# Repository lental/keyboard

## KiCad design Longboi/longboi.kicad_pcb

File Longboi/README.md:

http://www.keyboard-layout-editor.com/#/gists/9dde3a739abcb1b83a87db58105d393a

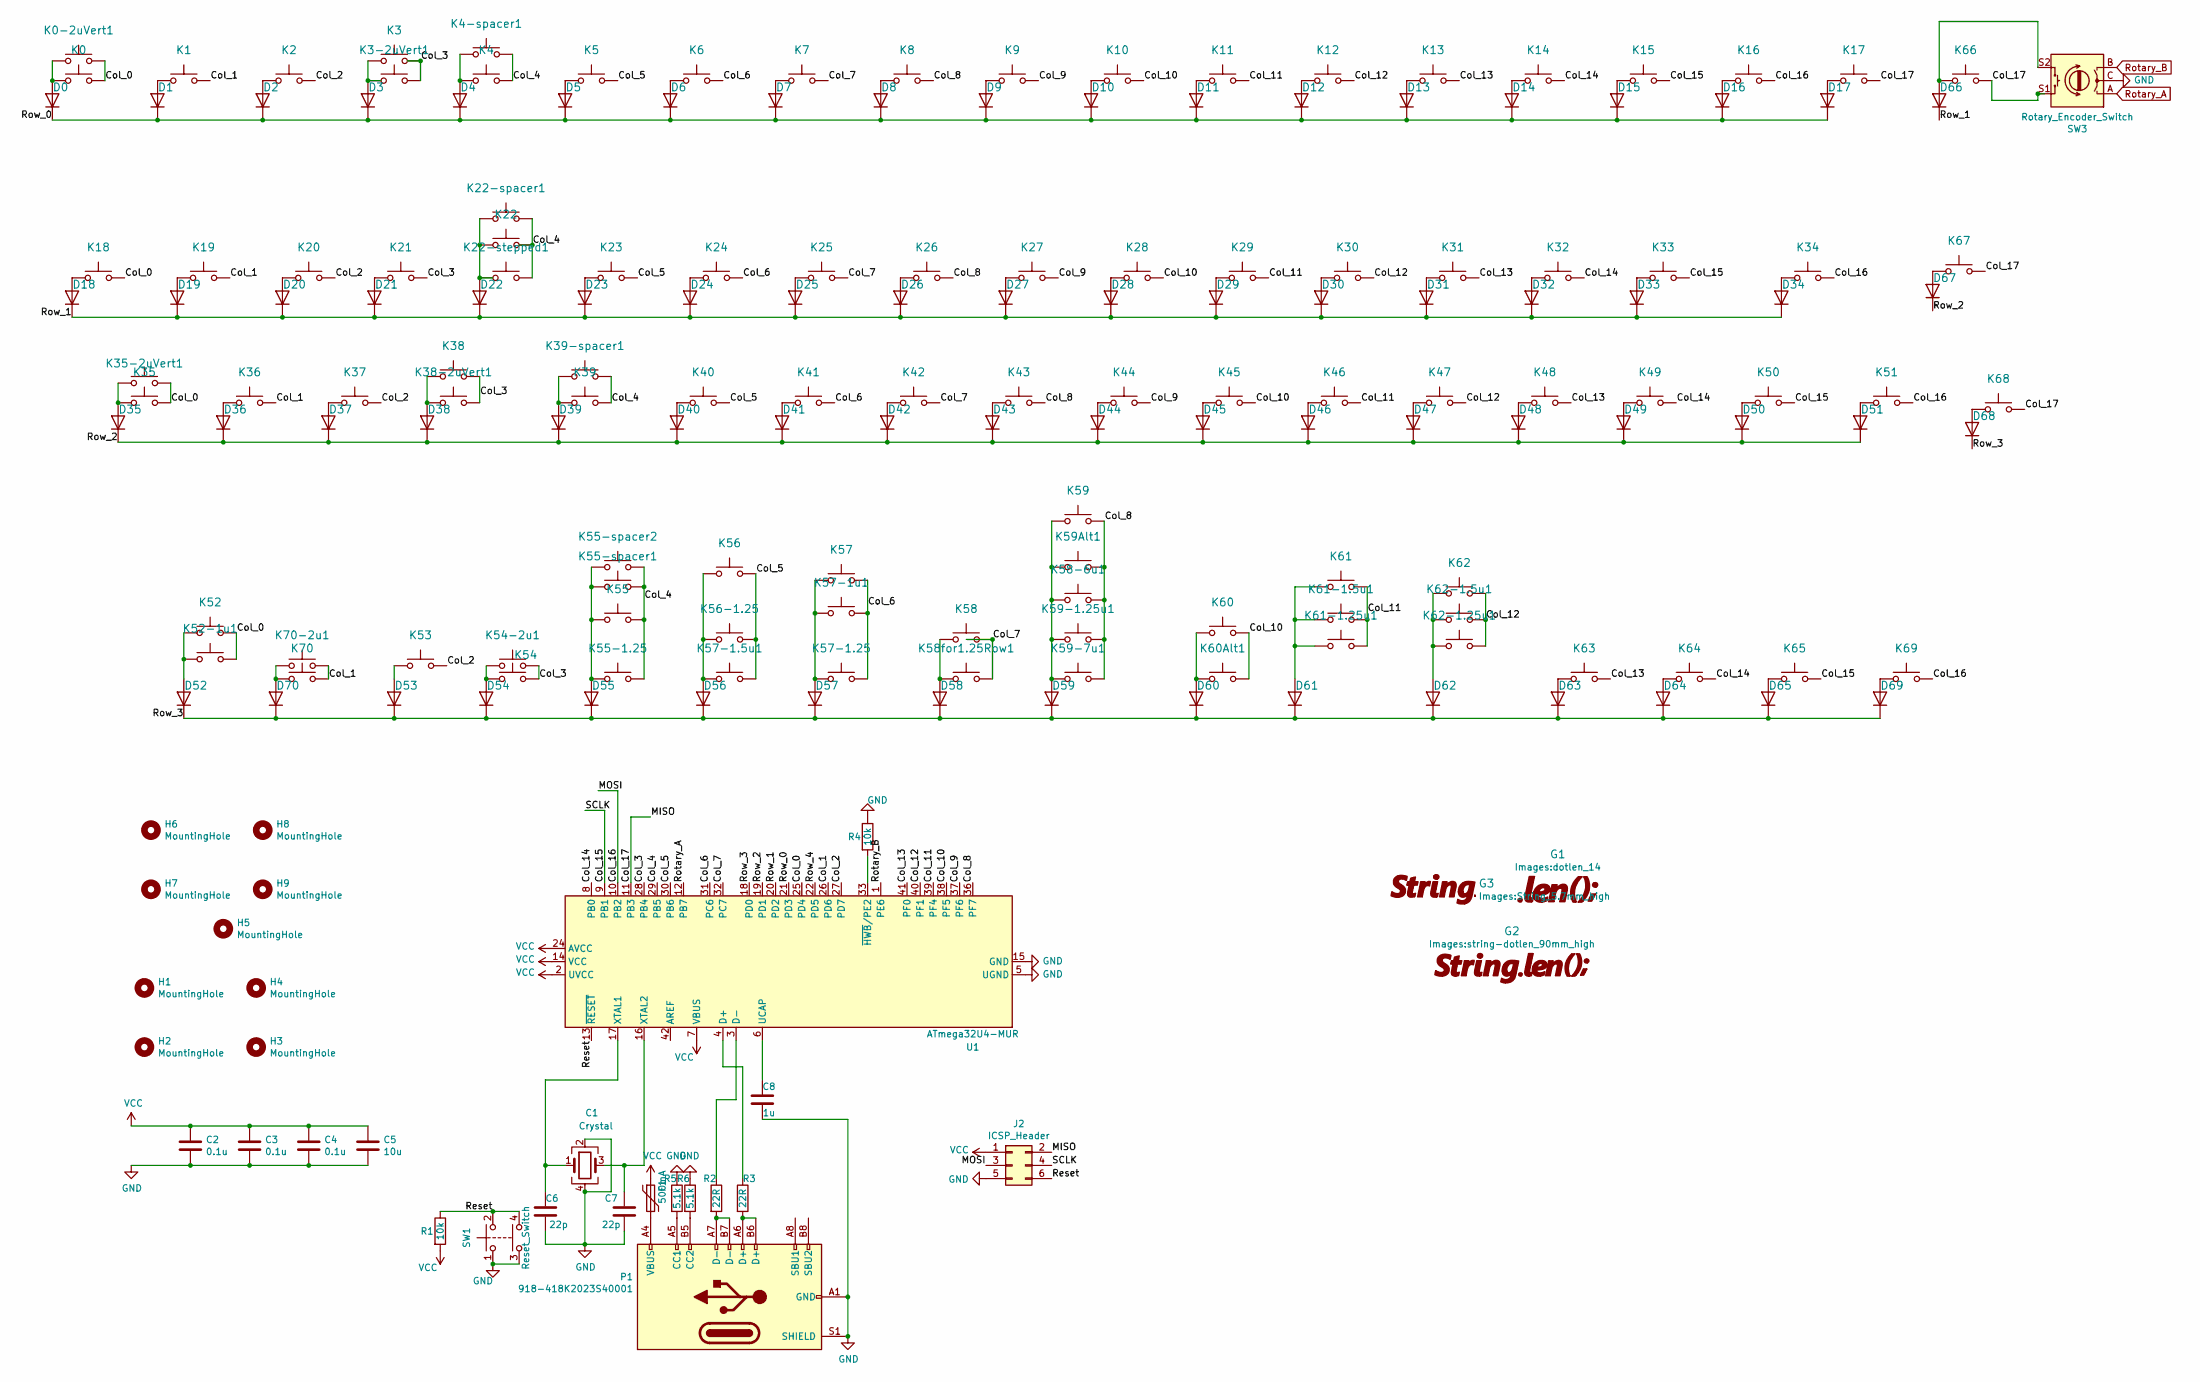
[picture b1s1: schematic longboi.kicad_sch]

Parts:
C1: Crystal; Crystal_SMD_3225-4Pin_3.2x2.5mm
C2, C3, C4: 0.1u; C_0805_2012Metric_Pad1.15x1.40mm_HandSolder
C5: 10u; C_0805_2012Metric_Pad1.15x1.40mm_HandSolder
C6, C7: 22p; C_0805_2012Metric_Pad1.15x1.40mm_HandSolder
C8: 1u; C_0805_2012Metric_Pad1.15x1.40mm_HandSolder
D0, D1, D2, D3, D4, D5, D6, D7, D8, D9, D10, D11, D12, D13, D14, D15, D16, D17, D18, D19, D20, D21, D22, D23, D24, D25, D26, D27, D28, D29, D30, D31, D32, D33, D34, D35, D36, D37, D38, D39, D40, D41, D42, D43, D44, D45, D46, D47, D48, D49, D50, D51, D52, D53, D54, D55, D56, D57, D58, D59, D60, D61, D62, D63, D64, D65, D66, D67, D68, D69, D70: SOD-323F; D_SOD-323F
F1: 500mA; Fuse_1206_3216Metric
G1: dotlen; dotlen_14
G2: string_dotlen; string-dotlen_90mm_high
G3: string; String_5.7mm_high
H1, H2, H3, H4, H5, H6, H7, H8, H9: MountingHole; M2 Mounting Hole
J2: ICSP_Header; PinHeader_2x03_P2.54mm_Vertical
K0, K1, K2, K3, K4-spacer1, K5, K6, K7, K8, K9, K10, K11, K12, K13, K14, K15, K16, K18, K19, K20, K21, K23, K24, K25, K26, K27, K28, K29, K30, K31, K32, K33, K35, K36, K37, K38, K40, K41, K42, K43, K44, K45, K46, K47, K48, K49, K51, K52-1u1, K53, K54, K55-spacer2, K57-1u1, K59, K60Alt1, K61, K62, K63, K64, K65, K66, K67, K68, K69, K70: KEYSW; MXOnly-1U-NoLED
K0-2uVert1, K35-2uVert1, K52, K54-2u1, K70-2u1: KEYSW; MXOnly-2U-ReversedStabilizers-NoLED
K3-2uVert1, K38-2uVert1: KEYSW; MXOnly-2U-NoLED
K4, K17, K55, K57-1.5u1, K61-1.5u1, K62-1.5u1: KEYSW; MXOnly-1.5U-NoLED
K22, K39-spacer1, K50: KEYSW; MXOnly-1.75U-NoLED
K22-spacer1, K22-stepped1, K55-1.25, K55-spacer1, K56, K56-1.25, K57, K57-1.25, K59-1.25u1, K61-1.25u1, K62-1.25u1: KEYSW; MXOnly-1.25U-NoLED
K34, K39, K58, K58for1.25Row1: KEYSW; MXOnly-2.25U-ReversedStabilizers-NoLED
K58-6u1: KEYSW; MXOnly-6.25U-ReversedStabilizers-NoLED
K59-7u1: KEYSW; MXOnly-7U-ReversedStabilizers-NoLED
K59Alt1, K60: KEYSW; MXOnly-2.75U-ReversedStabilizers-NoLED
P1: 918-418K2023S40001
R1, R4: 10k; R_0805_2012Metric_Pad1.15x1.40mm_HandSolder
R2, R3: 22R; R_0805_2012Metric_Pad1.15x1.40mm_HandSolder
R5, R6: 5.1k; R_0805_2012Metric_Pad1.15x1.40mm_HandSolder
SW1: Reset_Switch; SKQG-1155865
SW3: Rotary_Encoder_Switch; RotaryEncoder_Alps_EC11E-Switch_Vertical_H20mm_MX-1U
U1: ATmega32U4-MUR; QFN-44-1EP_7x7mm_P0.5mm_EP5.2x5.2mm

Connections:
/Col_0: K0.2, K0-2uVert1.2, K18.2, K35.2, K35-2uVert1.2, K52.2, K52-1u1.2, U1.25 (PD4)
/Col_1: K1.2, K19.2, K36.2, K70.2, K70-2u1.2, U1.26 (PD6)
/Col_2: K2.2, K20.2, K37.2, K53.2, U1.27 (PD7)
/Col_3: K3.2, K3-2uVert1.2, K21.2, K38.2, K38-2uVert1.2, K54.2, K54-2u1.2, U1.28 (PB4)
/Col_4: K4.2, K4-spacer1.2, K22.2, K22-spacer1.2, K22-stepped1.2, K39.2, K39-spacer1.2, K55.2, K55-1.25.2, K55-spacer1.2, K55-spacer2.2, U1.29 (PB5)
/Col_5: K5.2, K23.2, K40.2, K56.2, K56-1.25.2, K57-1.5u1.2, U1.30 (PB6)
/Col_6: K6.2, K24.2, K41.2, K57.2, K57-1.25.2, K57-1u1.2, U1.31 (PC6)
/Col_7: K7.2, K25.2, K42.2, K58.2, K58for1.25Row1.2, U1.32 (PC7)
/Col_8: K8.2, K26.2, K43.2, K58-6u1.2, K59.2, K59-1.25u1.2, K59-7u1.2, K59Alt1.2, U1.36 (PF7)
/Col_9: K9.2, K27.2, K44.2, U1.37 (PF6)
/Col_10: K10.2, K28.2, K45.2, K60.2, K60Alt1.2, U1.38 (PF5)
/Col_11: K11.2, K29.2, K46.2, K61.2, K61-1.5u1.2, K61-1.25u1.2, U1.39 (PF4)
/Col_12: K12.2, K30.2, K47.2, K62.2, K62-1.5u1.2, K62-1.25u1.2, U1.40 (PF1)
/Col_13: K13.2, K31.2, K48.2, K63.2, U1.41 (PF0)
/Col_14: K14.2, K32.2, K49.2, K64.2, U1.8 (PB0)
/Col_15: J2.4, K15.2, K33.2, K50.2, K65.2, U1.9 (PB1)
/Col_16: J2.3, K16.2, K34.2, K51.2, K69.2, U1.10 (PB2)
/Col_17: J2.2, K17.2, K66.2, K67.2, K68.2, SW3.S1, U1.11 (PB3)
/Reset: J2.6, R1.1, SW1.2, SW1.4, U1.13 (~RESET)
/Row_0: D0.1 (K), D1.1 (K), D2.1 (K), D3.1 (K), D4.1 (K), D5.1 (K), D6.1 (K), D7.1 (K), D8.1 (K), D9.1 (K), D10.1 (K), D11.1 (K), D12.1 (K), D13.1 (K), D14.1 (K), D15.1 (K), D16.1 (K), D17.1 (K), U1.21 (PD3)
/Row_1: D18.1 (K), D19.1 (K), D20.1 (K), D21.1 (K), D22.1 (K), D23.1 (K), D24.1 (K), D25.1 (K), D26.1 (K), D27.1 (K), D28.1 (K), D29.1 (K), D30.1 (K), D31.1 (K), D32.1 (K), D33.1 (K), D34.1 (K), D66.1 (K), U1.20 (PD2)
/Row_2: D35.1 (K), D36.1 (K), D37.1 (K), D38.1 (K), D39.1 (K), D40.1 (K), D41.1 (K), D42.1 (K), D43.1 (K), D44.1 (K), D45.1 (K), D46.1 (K), D47.1 (K), D48.1 (K), D49.1 (K), D50.1 (K), D51.1 (K), D67.1 (K), U1.19 (PD1)
/Row_3: D52.1 (K), D53.1 (K), D54.1 (K), D55.1 (K), D56.1 (K), D57.1 (K), D58.1 (K), D59.1 (K), D60.1 (K), D61.1 (K), D62.1 (K), D63.1 (K), D64.1 (K), D65.1 (K), D68.1 (K), D69.1 (K), D70.1 (K), U1.18 (PD0)
/Row_4: U1.22 (PD5)
GND: C1.2, C1.4, C2.2, C3.2, C4.2, C5.2, C6.2, C7.2, C8.2, J2.5, P1.A1 (GND), P1.A12 (GND), P1.B1 (GND), P1.B12 (GND), P1.S1 (SHIELD), R4.1, R5.1, R6.1, SW1.1, SW1.3, SW3.C, U1.5 (UGND), U1.15 (GND), U1.23 (GND), U1.35 (GND), U1.43 (GND), U1.45 (GND)
unnamed: C1.1, C6.1, U1.17 (XTAL1)
unnamed: C1.3, C7.1, U1.16 (XTAL2)
unnamed: C8.1, U1.6 (UCAP)
unnamed: D0.2 (A), K0.1, K0-2uVert1.1
unnamed: D1.2 (A), K1.1
unnamed: D2.2 (A), K2.1
unnamed: D3.2 (A), K3.1, K3-2uVert1.1
unnamed: D4.2 (A), K4.1, K4-spacer1.1
unnamed: D5.2 (A), K5.1
unnamed: D6.2 (A), K6.1
unnamed: D7.2 (A), K7.1
unnamed: D8.2 (A), K8.1
unnamed: D9.2 (A), K9.1
unnamed: D10.2 (A), K10.1
unnamed: D11.2 (A), K11.1
unnamed: D12.2 (A), K12.1
unnamed: D13.2 (A), K13.1
unnamed: D14.2 (A), K14.1
unnamed: D15.2 (A), K15.1
unnamed: D16.2 (A), K16.1
unnamed: D17.2 (A), K17.1
unnamed: D18.2 (A), K18.1
unnamed: D19.2 (A), K19.1
unnamed: D20.2 (A), K20.1
unnamed: D21.2 (A), K21.1
unnamed: D22.2 (A), K22.1, K22-spacer1.1, K22-stepped1.1
unnamed: D23.2 (A), K23.1
unnamed: D24.2 (A), K24.1
unnamed: D25.2 (A), K25.1
unnamed: D26.2 (A), K26.1
unnamed: D27.2 (A), K27.1
unnamed: D28.2 (A), K28.1
unnamed: D29.2 (A), K29.1
unnamed: D30.2 (A), K30.1
unnamed: D31.2 (A), K31.1
unnamed: D32.2 (A), K32.1
unnamed: D33.2 (A), K33.1
unnamed: D34.2 (A), K34.1
unnamed: D35.2 (A), K35.1, K35-2uVert1.1
unnamed: D36.2 (A), K36.1
unnamed: D37.2 (A), K37.1
unnamed: D38.2 (A), K38.1, K38-2uVert1.1
unnamed: D39.2 (A), K39.1, K39-spacer1.1
unnamed: D40.2 (A), K40.1
unnamed: D41.2 (A), K41.1
unnamed: D42.2 (A), K42.1
unnamed: D43.2 (A), K43.1
unnamed: D44.2 (A), K44.1
unnamed: D45.2 (A), K45.1
unnamed: D46.2 (A), K46.1
unnamed: D47.2 (A), K47.1
unnamed: D48.2 (A), K48.1
unnamed: D49.2 (A), K49.1
unnamed: D50.2 (A), K50.1
unnamed: D51.2 (A), K51.1
unnamed: D52.2 (A), K52.1, K52-1u1.1
unnamed: D53.2 (A), K53.1
unnamed: D54.2 (A), K54.1, K54-2u1.1
unnamed: D55.2 (A), K55.1, K55-1.25.1, K55-spacer1.1, K55-spacer2.1
unnamed: D56.2 (A), K56.1, K56-1.25.1, K57-1.5u1.1
unnamed: D57.2 (A), K57.1, K57-1.25.1, K57-1u1.1
unnamed: D58.2 (A), K58.1, K58for1.25Row1.1
unnamed: D59.2 (A), K58-6u1.1, K59.1, K59-1.25u1.1, K59-7u1.1, K59Alt1.1
unnamed: D60.2 (A), K60.1, K60Alt1.1
unnamed: D61.2 (A), K61.1, K61-1.5u1.1, K61-1.25u1.1
unnamed: D62.2 (A), K62.1, K62-1.5u1.1, K62-1.25u1.1
unnamed: D63.2 (A), K63.1
unnamed: D64.2 (A), K64.1
unnamed: D65.2 (A), K65.1
unnamed: D66.2 (A), K66.1, SW3.S2
unnamed: D67.2 (A), K67.1
unnamed: D68.2 (A), K68.1
unnamed: D69.2 (A), K69.1
unnamed: D70.2 (A), K70.1, K70-2u1.1
unnamed: F1.2, P1.A4 (VBUS), P1.A9 (VBUS), P1.B4 (VBUS), P1.B9 (VBUS)
unnamed: P1.A5 (CC1), R5.2
unnamed: P1.A6 (D+), P1.B6 (D+), R3.2
unnamed: P1.A7 (D-), P1.B7 (D-), R2.2
unnamed: P1.B5 (CC2), R6.2
unnamed: R2.1, U1.3 (D-)
unnamed: R3.1, U1.4 (D+)
unnamed: R4.2, U1.33 (~HWB/PE2)
Rotary_A: SW3.A, U1.12 (PB7)
Rotary_B: SW3.B, U1.1 (PE6)
VCC: C2.1, C3.1, C4.1, C5.1, F1.1, J2.1, R1.2, U1.2 (UVCC), U1.7 (VBUS), U1.14 (VCC), U1.24 (AVCC), U1.34 (VCC), U1.44 (AVCC)

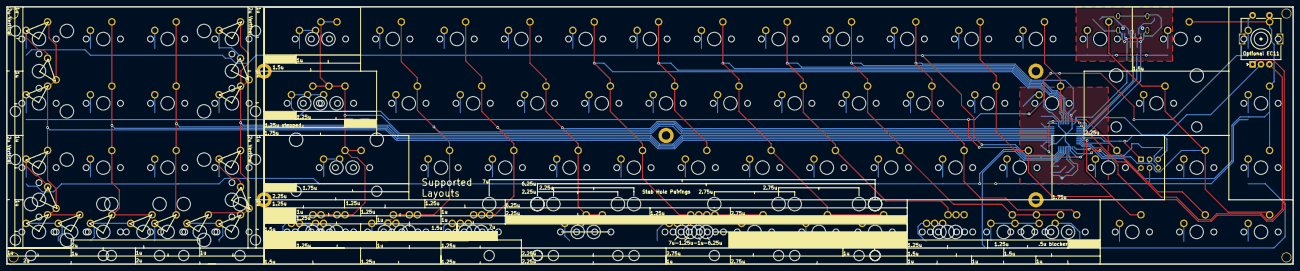
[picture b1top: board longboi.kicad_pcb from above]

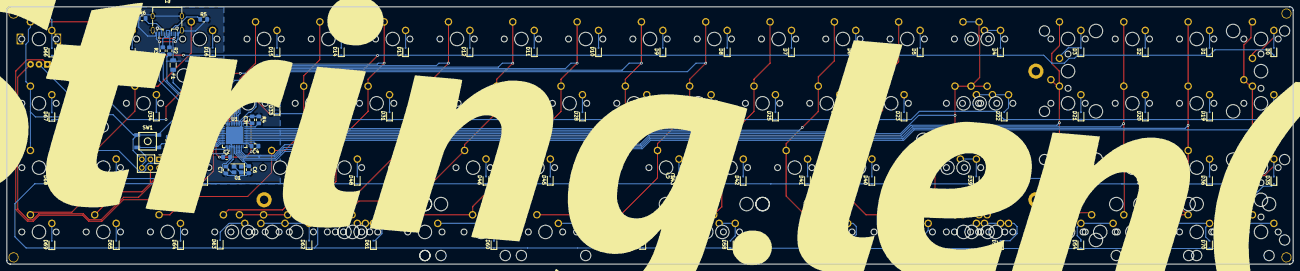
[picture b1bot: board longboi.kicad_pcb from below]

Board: 2 copper layers, 381.0 x 76.2 mm, 203 parts (91 on the bottom side), 109 nets.

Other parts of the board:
Ge: LOGO; beebo_10mm

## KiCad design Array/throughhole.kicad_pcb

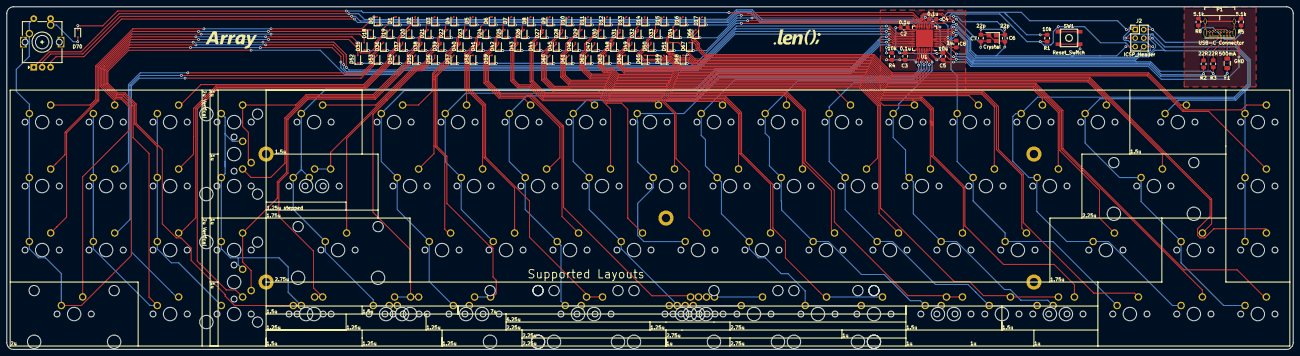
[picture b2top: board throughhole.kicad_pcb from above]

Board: 2 copper layers, 383.0 x 102.0 mm, 185 parts (1 on the bottom side), 110 nets.

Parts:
Array_Logo1: Array_Logo; array_logo_14
Array_Logo2: Array_Logo; array_dotlen_logo_526
C1: Crystal; Crystal_SMD_3225-4Pin_3.2x2.5mm
C2, C3, C4: 0.1u; C_0805_2012Metric_Pad1.15x1.40mm_HandSolder
C5: 10u; C_0805_2012Metric_Pad1.15x1.40mm_HandSolder
C6, C7: 22p; C_0805_2012Metric_Pad1.15x1.40mm_HandSolder
C8: 1u; C_0805_2012Metric_Pad1.15x1.40mm_HandSolder
D0, D1, D2, D3, D4, D5, D6, D7, D8, D9, D10, D11, D12, D13, D14, D15, D16, D17, D18, D19, D20, D21, D22, D23, D24, D25, D26, D27, D28, D29, D30, D31, D32, D33, D34, D35, D36, D37, D38, D39, D40, D41, D42, D43, D44, D45, D46, D47, D48, D49, D50, D51, D52, D53, D54, D55, D56, D57, D58, D59, D60, D61, D62, D63, D64, D65, D66, D67, D68, D69, D70: D; D_SOD-323F
F1: 500mA; Fuse_1206_3216Metric
G1: dotlen; dotlen_14
H1, H2, H3, H4, H5: MountingHole; M2 Mounting Hole
J2: ICSP_Header; PinHeader_2x03_P2.54mm_Vertical
K0, K1, K2, K3, K5, K6, K7, K8, K9, K10, K11, K12, K13, K14, K15, K16, K18, K19, K20, K21, K23, K24, K25, K26, K27, K28, K29, K30, K31, K32, K33, K35, K36, K37, K38, K40, K41, K42, K43, K44, K45, K46, K47, K48, K49, K51, K53, K54, K59, K60Alt1, K61, K62, K63, K64, K65, K66, K67, K68, K69: KEYSW; MXOnly-1U-NoLED
K3-2uVert1, K38-2uVert1, K52: KEYSW; MXOnly-2U-NoLED
K4, K17, K55, K57-1.5u1, K61-1.5u1, K62-1.5u1: KEYSW; MXOnly-1.5U-NoLED
K22, K50: KEYSW; MXOnly-1.75U-NoLED
K22-stepped1, K55-1.25, K56, K56-1.25, K57, K57-1.25, K59-1.25u1: KEYSW; MXOnly-1.25U-NoLED
K34, K39, K58, K58for1.25Row1: KEYSW; MXOnly-2.25U-NoLED
K58-6u1: KEYSW; MXOnly-6.25U-NoLED
K59-7u1: KEYSW; MXOnly-7U-NoLED
K59Alt1, K60: KEYSW; MXOnly-2.75U-NoLED
KEsc1: KEYSW; MXOnly-1U-NoLED
P1: USB-C Connector; USB_C_GCT_USB4085
R1, R4: 10k; R_0805_2012Metric_Pad1.15x1.40mm_HandSolder
R2, R3: 22R; R_0805_2012Metric_Pad1.15x1.40mm_HandSolder
R5, R6: 5.1k; R_0805_2012Metric_Pad1.15x1.40mm_HandSolder
SW1: Reset_Switch; SKQG-1155865
SW3: Rotary_Encoder_Switch; RotaryEncoder_Alps_EC11E-Switch_Vertical_H20mm_MX-1U
U1: ATmega32U4-MUR; QFN-44-1EP_7x7mm_P0.5mm_EP5.2x5.2mm

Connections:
/Col_0: K0.1, K18.1, K35.1, K52.1, KEsc1.1, SW3.S2, U1.25
/Col_1: K1.1, K19.1, K36.1, K53.1, U1.26
/Col_2: K2.1, K20.1, K37.1, K54.1, U1.27
/Col_3: K3.1, K3-2uVert1.1, K21.1, K38.1, K38-2uVert1.1, K55.1, K55-1.25.1, U1.28
/Col_4: K4.1, K22.1, K22-stepped1.1, K39.1, K56.1, K56-1.25.1, K57-1.5u1.1, U1.29
/Col_5: K5.1, K23.1, K40.1, K57.1, K57-1.25.1, U1.30
/Col_6: K6.1, K24.1, K41.1, U1.31
/Col_7: K7.1, K25.1, K42.1, K58.1, K58for1.25Row1.1, U1.32
/Col_8: K8.1, K26.1, K43.1, K58-6u1.1, K59.1, K59-1.25u1.1, K59-7u1.1, K59Alt1.1, U1.36
/Col_9: K9.1, K27.1, K44.1, U1.37
/Col_10: K10.1, K28.1, K45.1, K60.1, K60Alt1.1, U1.38
/Col_11: K11.1, K29.1, K46.1, K61.1, K61-1.5u1.1, U1.39
/Col_12: K12.1, K30.1, K47.1, K62.1, K62-1.5u1.1, U1.40
/Col_13: K13.1, K31.1, K48.1, K63.1, U1.41
/Col_14: K14.1, K32.1, K49.1, K64.1, U1.8
/Col_15: J2.4, K15.1, K33.1, K50.1, K65.1, U1.9
/Col_16: J2.3, K16.1, K34.1, K51.1, K69.1, U1.10
/Col_17: J2.2, K17.1, K66.1, K67.1, K68.1, U1.11
/Reset: J2.6, R1.1, SW1.2, SW1.4, U1.13
/Row_0: D0.1, D1.1, D2.1, D3.1, D4.1, D5.1, D6.1, D7.1, D8.1, D9.1, D10.1, D11.1, D12.1, D13.1, D14.1, D15.1, D16.1, D17.1, U1.19
/Row_1: D18.1, D19.1, D20.1, D21.1, D22.1, D23.1, D24.1, D25.1, D26.1, D27.1, D28.1, D29.1, D30.1, D31.1, D32.1, D33.1, D34.1, D66.1, U1.20
/Row_2: D35.1, D36.1, D37.1, D38.1, D39.1, D40.1, D41.1, D42.1, D43.1, D44.1, D45.1, D46.1, D47.1, D48.1, D49.1, D50.1, D51.1, D67.1, U1.21
/Row_3: D52.1, D53.1, D54.1, D55.1, D56.1, D57.1, D58.1, D59.1, D60.1, D61.1, D62.1, D63.1, D64.1, D65.1, D68.1, D69.1, U1.22
/Row_4: D70.1, U1.18
GND: C1.2, C1.4, C2.2, C3.2, C4.2, C5.2, C6.2, C7.2, C8.2, J2.5, P1.A1, P1.A12, P1.B1, P1.B12, P1.S1, R4.1, R5.1, R6.1, SW1.1, SW1.3, SW3.C, U1.5, U1.15, U1.23, U1.35, U1.43, U1.45
unnamed: C1.1, C6.1, U1.17
unnamed: C1.3, C7.1, U1.16
unnamed: C8.1, U1.6
unnamed: D0.2, K0.2
unnamed: D1.2, K1.2
unnamed: D2.2, K2.2
unnamed: D3.2, K3.2, K3-2uVert1.2
unnamed: D4.2, K4.2
unnamed: D5.2, K5.2
unnamed: D6.2, K6.2
unnamed: D7.2, K7.2
unnamed: D8.2, K8.2
unnamed: D9.2, K9.2
unnamed: D10.2, K10.2
unnamed: D11.2, K11.2
unnamed: D12.2, K12.2
unnamed: D13.2, K13.2
unnamed: D14.2, K14.2
unnamed: D15.2, K15.2
unnamed: D16.2, K16.2
unnamed: D17.2, K17.2
unnamed: D18.2, K18.2
unnamed: D19.2, K19.2
unnamed: D20.2, K20.2
unnamed: D21.2, K21.2
unnamed: D22.2, K22.2, K22-stepped1.2
unnamed: D23.2, K23.2
unnamed: D24.2, K24.2
unnamed: D25.2, K25.2
unnamed: D26.2, K26.2
unnamed: D27.2, K27.2
unnamed: D28.2, K28.2
unnamed: D29.2, K29.2
unnamed: D30.2, K30.2
unnamed: D31.2, K31.2
unnamed: D32.2, K32.2
unnamed: D33.2, K33.2
unnamed: D34.2, K34.2
unnamed: D35.2, K35.2
unnamed: D36.2, K36.2
unnamed: D37.2, K37.2
unnamed: D38.2, K38.2, K38-2uVert1.2
unnamed: D39.2, K39.2
unnamed: D40.2, K40.2
unnamed: D41.2, K41.2
unnamed: D42.2, K42.2
unnamed: D43.2, K43.2
unnamed: D44.2, K44.2
unnamed: D45.2, K45.2
unnamed: D46.2, K46.2
unnamed: D47.2, K47.2
unnamed: D48.2, K48.2
unnamed: D49.2, K49.2
unnamed: D50.2, K50.2
unnamed: D51.2, K51.2
unnamed: D52.2, K52.2
unnamed: D53.2, K53.2
unnamed: D54.2, K54.2
unnamed: D55.2, K55.2, K55-1.25.2
unnamed: D56.2, K56.2, K56-1.25.2, K57-1.5u1.2
unnamed: D57.2, K57.2, K57-1.25.2
unnamed: D58.2, K58.2, K58for1.25Row1.2
unnamed: D59.2, K58-6u1.2, K59.2, K59-1.25u1.2, K59-7u1.2, K59Alt1.2
unnamed: D60.2, K60.2, K60Alt1.2
unnamed: D61.2, K61.2, K61-1.5u1.2
unnamed: D62.2, K62.2, K62-1.5u1.2
unnamed: D63.2, K63.2
unnamed: D64.2, K64.2
unnamed: D65.2, K65.2
unnamed: D66.2, K66.2
unnamed: D67.2, K67.2
unnamed: D68.2, K68.2
unnamed: D69.2, K69.2
unnamed: D70.2, KEsc1.2, SW3.S1
unnamed: F1.2, P1.A4, P1.A9, P1.B4, P1.B9
unnamed: P1.A5, R5.2
unnamed: P1.A6, P1.B6, R3.2
unnamed: P1.A7, P1.B7, R2.2
unnamed: P1.B5, R6.2
unnamed: R2.1, U1.3
unnamed: R3.1, U1.4
unnamed: R4.2, U1.33
Rotary_A: SW3.A, U1.12
Rotary_B: SW3.B, U1.1
VCC: C2.1, C3.1, C4.1, C5.1, F1.1, J2.1, R1.2, U1.2, U1.7, U1.14, U1.24, U1.34, U1.44

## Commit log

2021-12-22 remove production outputs
2021-12-31 Rename and shuffle Longboi into its own folder
    Rename and shuffle Longboi into its own folder
2021-12-31 Add Array.len()
2022-01-06 add qmk and via files
2022-01-06 tweak readme
2022-01-09 updatekeymaps
2022-01-16 update LongBoi for second prototype
    update LongBoi for second prototype
2022-01-16 some array changes
2022-01-16 clean up last prototype files
2022-01-17 update longboi to what was ordered from jlcpcb
2022-01-25 update longboi to be slightly newer than ordered
2022-01-25 fix bug in longboi...
    key38 was not schematiced right
2022-01-27 added map.len()
2022-01-28 CLean up gitignore, update map
2022-01-28 update map, delete some old fi les
2022-01-28 Start List.len
2022-02-12 created rev2 firmware
2022-02-13 clean up map and string with prototype fixes
2022-02-13 moreupdates to tweak the two keyboards
2022-02-13 some more tweaks on keyboards
2022-03-12 probably buying all three now
2022-03-12 now purchasing
2022-04-07 add listlen, update stringlen for the third build
2022-04-08 made map.len via qmk
2022-04-08 clean up keymaps for map and list
2022-05-08 Update List and Map
    Update List and Map
